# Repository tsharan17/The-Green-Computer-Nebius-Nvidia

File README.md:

<div align="center">

# The Green Computer

## ***"The Sustainable Tech of 21st Century"***

**See how an AI model will run on your hardware, before you build it.**<br>
Predict latency, power, heat, throttling, cost and carbon. Get ranked fixes. Verify. Export.

**[Try it live](https://green-computer-7yy6xwxdna-ue.a.run.app)** ·
**[Two-minute tour](docs/demo-guide.md)** ·
**[Architecture](docs/architecture.md)** ·
**[Run it yourself](#run-it-yourself)**

<table>
  <tr>
    <td align="center" width="25%"><h3>🔮 Predict</h3><sub>Power, heat and throttling solved together, <b>before the hardware exists</b></sub></td>
    <td align="center" width="25%"><h3>💡 Recommend</h3><sub>Ranked fixes across model, software, settings, board and cooling</sub></td>
    <td align="center" width="25%"><h3>⚡ See the impact</h3><sub>Click a change: the engine <b>re-runs everything</b> and shows today vs with the change</sub></td>
    <td align="center" width="25%"><h3>🛡️ Trust it</h3><sub>Nemotron explains; the engine computes. A guardrail rejects any invented number</sub></td>
  </tr>
</table>

> **What is new:** a co-design loop where **NVIDIA Nemotron proposes ideas but a deterministic physics
> engine evaluates every one**, so each recommendation arrives with its own computed before/after.
> [Read why it is innovative ›](#why-it-is-innovative)

*Nebius x NVIDIA Global AI Hackathon, Best Apps and Agents track*

</div>

---

## Contents

[The problem](#the-problem) · [See it](#see-it) · [Try it live](#try-it-live-in-two-minutes) ·
[Nemotron and Token Factory](#built-on-nvidia-nemotron-and-nebius-token-factory) ·
[Why it is different](#why-it-is-different) · [Innovation](#why-it-is-innovative) · [Recommendations](#recommendations-see-the-impact-of-every-change) · [Features](#features) · [How it works](#how-it-works) ·
[Run it yourself](#run-it-yourself) · [Tests](#tests) · [Status](#what-is-and-is-not-verified) ·
[Tech stack](#tech-stack) · [Licence](#licence)

## The problem

> [!IMPORTANT]
> Teams put AI on robots, cameras and edge boards, then discover **too late** that the model
> overheats, throttles itself, blows the power budget or sits on the wrong board. Fixing it means
> weeks of trial and error across the model, the software and the hardware.

**The Green Computer shows it before anything is built.** The bundled example, a YOLOv8s detector on
a Jetson Orin NX at 30 inputs a second in a 40 °C room:

| | Today | With the recommended plan |
|---|:---:|:---:|
| **Verdict** | ❌ Fails | ✅ Passes every requirement |
| **Chip temperature** | 🔥 90 °C, throttles to ~70% speed | ❄️ within your limits |
| **Power** | baseline | **about 59% less** |
| **Energy per input** | baseline | **-72%** |

Then it exports a report and a recipe of scripts. Everything is vendor-neutral and runs fully
offline; NVIDIA GPUs, Nebius cloud jobs and the AI assistant are optional accelerators.

## See it

<table>
  <tr>
    <td width="50%"><br><sub><b>1. Analyse today's setup.</b> A plain verdict, what limits it, and the numbers against your limits.</sub></td>
    <td width="50%"><br><sub><b>2. Try ranked changes.</b> The engine re-runs everything with each one: -72% energy, 59% less power.</sub></td>
  </tr>
  <tr>
    <td colspan="2"><br><sub><b>3. See why.</b> Board heat map: the compute engine reaches 90 °C and slows itself down to cool off.</sub></td>
  </tr>
</table>

<sub>Screenshots are from a local copy running without a Token Factory key, so the Green Agent box
says it is not configured. In the hosted demo it is on.</sub>

## Try it live in two minutes

Open **[green-computer-7yy6xwxdna-ue.a.run.app](https://green-computer-7yy6xwxdna-ue.a.run.app)**
(free, no payment, no email confirmation), then:

1. **Sign up** and open **Example: YOLOv8s on a robot (30 FPS, 55 W, 40 °C)**.
2. **Analyse.** Today's setup fails: the Jetson Orin NX overheats and throttles to about 70% of its speed.
3. **Recommendations.** Click **Start with the top-ranked change**; the engine re-runs everything with it.
4. **Validation.** Build a plan: it meets every requirement with about 59% less power.
5. **Ask the assistant** (sidebar): Nemotron answers by calling the engine, and every figure is checked.
6. **Datasheet import** (Inputs > Hardware, "Your hardware isn't in the list?"): try "Hailo-8L".
7. **Export** the report and the recipe.

## Built on NVIDIA Nemotron and Nebius Token Factory

The deterministic engine computes every number. **NVIDIA Nemotron models, called at run time through
the Nebius Token Factory inference API** (OpenAI-compatible, `TOKEN_FACTORY_API_KEY`), explain and
suggest. Each tier does the job it suits:

| Nemotron model | Job | Why that model | Code |
|---|---|---|---|
| **Nemotron 3 Ultra** | **Green Agent**: plans, calls the engine as tools, explains results | Multi-step reasoning and tool use | `backend/app/agent/` |
| **Nemotron 3 Super** | **AI candidates**: extra change ideas as schema-checked JSON | Mid-weight reasoning at lower cost | `backend/app/agent/recommender.py` |
| **Nemotron 3 Nano** | **Datasheet import**: reads specs from pages found by **Tavily** | Fast, cheap extraction | `backend/app/agent/datasheet.py`, `backend/app/integrations/tavily.py` |

### How the model is kept honest

```mermaid
flowchart LR
    Q([Your question]) --> A[Nemotron agent]
    A -->|asks| E[Engine tools]
    E -->|numbers + provenance| A
    A --> G{Guardrail}
    G -->|every figure is in a tool result| R([Answer])
    G -->|unsupported figure| X([Rejected])
```

| Guard | What it does |
|---|---|
| 🛡️ **Number guardrail** | Rejects any figure in a reply that is not in a tool result |
| 🔒 **Read-only requirements** | The agent cannot change your limits to make a result pass |
| 🧾 **Schema-checked candidates** | Unknown change ids lose their link, unsupported figures are removed, each is labelled *not evaluated* until the engine runs it |
| 👤 **Human confirmation** | Datasheet values arrive with their source page; a person confirms them |
| 🔌 **Live model matching** | Ids are matched against the provider's own list (`GC_MODEL_ULTRA`, `GC_MODEL_SUPER`, `GC_MODEL_NANO` override). All three are live in the [hosted demo](https://green-computer-7yy6xwxdna-ue.a.run.app) |

### Where Token Factory helped

| | Benefit | In practice |
|---|---|---|
| 🚀 | **No GPU needed to use Nemotron** | Built on a machine without an NVIDIA GPU; one OpenAI-compatible endpoint serves Ultra, Super and Nano to any laptop and the cloud demo |
| ⚖️ | **Right-sized models** | Ultra: tool-calling agent, ~1.4 s for a short reply. Super: six candidates in 12 to 21 s. Nano: whole search-and-extract datasheet import in 45 to 60 s (including Tavily) |
| 🔁 | **Swappable** | `TOKEN_FACTORY_BASE_URL` and `GC_MODEL_*` point the same code at any OpenAI-compatible endpoint; `scripts/check_nebius.py` checks chat and a tool-call round trip |

### Services used

| Service | Use | Status |
|---|---|---|
| Nebius Token Factory + NVIDIA Nemotron (Ultra, Super, Nano) | Agent, candidates, datasheet extraction | Live, verified 27 Oct 2026 |
| Tavily | Datasheet search for hardware not in the library | Live, verified 27 Oct 2026 |
| Nebius Serverless Jobs (NVIDIA GPUs) | Real benchmarks for calibration (`bench/`, `GC_ENABLE_NEBIUS=1`) | Built, not run live |
| Nebius Serverless Endpoints | Hosting the app ([deploy/endpoint.md](deploy/endpoint.md)) | Built, not run live |
| Google Cloud Run + Neon PostgreSQL | Hosts the public demo ([deploy/cloudrun/](deploy/cloudrun/README.md)) | Live |

Nebius Serverless Jobs and Endpoints are documented in [docs/connecting-nebius.md](docs/connecting-nebius.md)
and off by default (`GC_ENABLE_NEBIUS=0`).

## Why it is different

<table>
  <tr>
    <td width="25%" valign="top"><h3>📏 Honest numbers</h3>Every metric carries a <code>low..high</code> range and a source: analytical, calibrated, measured, vendor spec or assumed. Predictions are never shown as measurements.</td>
    <td width="25%" valign="top"><h3>🧮 The model never invents</h3>The language model explains and proposes. The engine decides, and every figure is traceable to a tool result.</td>
    <td width="25%" valign="top"><h3>🧭 One coherent path</h3>Inputs, verification, analysis, recommendations, validation, export: a numbered stepper, Back / Next on every page, example projects, light and dark themes.</td>
    <td width="25%" valign="top"><h3>🚧 Clear about gaps</h3>Unsupported inputs (schematic, PCB, RTL, netlist, assembly) get a "planned" message naming the format needed, never a fake success. Requirements are never loosened to pass.</td>
  </tr>
</table>

## Why it is innovative

Most tools answer one question about one layer: a profiler measures a model on hardware you already
own, a simulator models a chip, a spreadsheet adds up watts. The Green Computer closes the loop across
all of them **before the hardware exists**, in a single path.

| | Typical tools | **The Green Computer** |
|---|---|---|
| **When you learn about heat and throttling** | After you buy and run the board | Before: power, temperature and throttling are solved together |
| **Scope** | One layer: the model, or the runtime, or the chip | Model, software, hardware settings, board and cooling choice in one search |
| **What you get** | A number, or a dashboard | A verdict, the limiting factor, ranked fixes, and the re-analysed result of each |
| **Trust** | A single figure | A `low..high` range with provenance on every metric; predicted and measured never mixed |
| **Role of AI** | Often a chatbot that may invent figures | Nemotron explains and proposes; a guardrail rejects any number the engine did not compute |
| **Vendor lock-in** | Tied to one vendor's silicon | Vendor-neutral library of boards, MCUs, FPGAs and accelerators, or describe your own |
| **Outcome** | Insight | A report, a plan and a recipe of scripts you can act on |

What is new, in one line: **a co-design loop where a language model proposes ideas but a deterministic
physics engine evaluates every one of them, so each recommendation arrives with its own computed
before/after, not a guess.** (We make no claim that nothing similar exists anywhere; this is the
combination we built and verified, with its limits stated below.)

## Recommendations: see the impact of every change

Recommendations are the heart of the app. Nothing is suggested without being **evaluated**: click any
change and the engine re-runs the whole analysis with it applied, so you see the consequence on your
system, not a rule of thumb.

```mermaid
flowchart LR
    A[Today's setup<br/>❌ fails] --> B[Ranked changes<br/>5 levels]
    B -->|click one| C[Engine re-runs<br/>the full analysis]
    C --> D[New verdict +<br/>what moved]
    D --> E[Same four figures<br/>today vs with the change]
    E -->|combine changes| F[Plan: each alone<br/>vs together vs today]
    F --> G[Export report<br/>+ recipe scripts]
```

| Level | Example changes | What you see change |
|---|---|---|
| 🧠 **The AI model** | Quantise (FP16 / INT8), prune, smaller input, a lighter model | Energy, throughput, accuracy risk |
| ⚙️ **How it runs** | Batching, runtime options | Latency, throughput, memory |
| 🎛️ **Hardware settings** | Power mode, clocks | Power, temperature, throttling |
| 🔌 **Hardware or cooling** | Another board, a bigger heatsink or other cooling | Steady-state temperature, headroom |
| 💡 **Chip and board ideas** | Directional what-ifs, labelled as such | Direction of change only |

**What the impact view shows, for each change you try:**

- the **new verdict** (fails to passes, or what still fails and why),
- **what moves**: latency, energy per input, power, peak temperature, throttling, cost and carbon,
- the **same four figures side by side, today and with the change**: board heat map, warm-up curve,
  where the energy goes, and power over a batch,
- a **confidence level** and the range on every number.

In the bundled example the top-ranked plan turns a failing Jetson Orin NX into a pass with
**-72% energy and about 59% less power**, and the plan builder shows each change alone and all of
them together against today. Changes are ranked to fix failing requirements first, then your
priority, and each unit of engineering effort costs a little in the ranking so a physical change has
to earn its place. Requirements are never loosened to make a result pass.

## Features

<details open>
<summary><b>The six-step path</b></summary>

1. **Workspace.** Create an account; projects live in a private or a team workspace. Every change of
   inputs is a version; every analysis, plan, upload and export is in the project's history.
2. **Model and hardware.** Upload an ONNX model (validated, with a graph summary) or pick one of the
   library models; pick a board, MCU, FPGA or accelerator from the library or describe your own.
   Each hardware category lists exactly which files it accepts: device profiles (YAML/JSON, values
   may carry units), Vivado / ST Edge AI / Vela reports, power and telemetry logs, firmware ELF
   files, datasheets (read offline; scans go to OCR when installed, otherwise manual review).
3. **Constraints and environment.** Throughput, power, latency, memory and accuracy limits; ambient
   temperature, cooling, hours of use, electricity price and grid carbon; how it runs today.
4. **Analysis (of today's setup only).** The verdict, what limits it, the numbers against your
   limits, and four figures: a board heat map, the warm-up curve, where the energy goes and power
   over one batch. Optional detail views: **system map**, **execution timeline**, **memory map**,
   **thermal and cooling** and **energy and performance**.
5. **Recommendations: try changes.** Changes at five levels: the AI model, how it runs, hardware
   settings, hardware or cooling choice, and directional chip/board ideas, ranked for your
   requirements. Click one and the engine re-runs the analysis with it. Optionally ask Nemotron for
   more candidates; nothing it proposes is applied until the engine evaluates it.
6. **Validation and export.** Combine changes into a plan; the engine re-analyses today, each change
   alone and the combination. Run the model on the server's CPU (ONNX Runtime, isolated and
   time-limited) for measured latency; import measurements (bench JSON, CSV, nvidia-smi, tegrastats);
   compare predicted with measured. Export the report (Markdown, HTML, PDF), plan JSON, comparisons,
   traces, a hardware change specification, deployment configuration, recipe scripts, and an INT8
   ONNX model when quantisation runs and its outputs match the original.

</details>

<details>
<summary><b>Honesty rules</b></summary>

- Every number carries its range and its source. Predicted traces are labelled predicted; only real
  runs or imported logs are measured, and the two are never mixed.
- Exports are labelled *generated and validated*, *generated* or *template*. No changed PCB, RTL or
  chip-design file is ever produced; chip and board ideas are directional what-ifs.
- Accuracy effects of quantisation or pruning are priors with stated risk, never promises.
- The optional AI assistant cannot produce numbers; the engine computes all of them.

</details>

## How it works

```mermaid
flowchart LR
    U([Browser<br/>React + Vite]) -->|/api/v1| API[FastAPI<br/>auth, tenancy, services]
    API --> ENG[Engine<br/>roofline, power-temperature-<br/>throttling solver, search]
    API --> TWIN[Digital twin<br/>predicted and measured traces]
    API --> DB[(SQLite or<br/>PostgreSQL)]
    API --> EXEC[Isolated worker<br/>ONNX Runtime benchmark,<br/>INT8 quantisation]
    API -->|tool calls, JSON| TF[Nebius Token Factory<br/>NVIDIA Nemotron<br/>Ultra / Super / Nano]
    TF -.->|explains, proposes| API
    API -->|datasheet search| TV[Tavily]
    EXEC -.->|optional| NB[Nebius Serverless Jobs<br/>NVIDIA GPUs]
```

The engine is pure and deterministic (no network, no LLM). The Nemotron layer sits beside it and can
only call it as a tool. The full description, with a status for each part, is in
[docs/architecture.md](docs/architecture.md).

<details>
<summary><b>Repository map</b></summary>

| Path | What is in it |
|---|---|
| `backend/app/engine/` | Physics, search and advice (pure, deterministic) |
| `backend/app/twin/` | Digital twin: execution trace, tensor lifetimes, memory timeline |
| `backend/app/agent/` | Nemotron on Token Factory: agent, recommender, datasheet import, guardrail |
| `backend/app/api/v1/`, `services/`, `db/`, `auth/` | API, orchestration, models, accounts and tenancy |
| `backend/app/execution/` | Isolated worker: benchmark, quantise, compare |
| `backend/app/migrations/` | Alembic revisions |
| `frontend/src/` | React app and hand-built SVG charts (`twin/chart.tsx`) |
| `frontend/e2e/` | Playwright browser journeys and accessibility checks |
| `bench/` | Benchmark scripts for GPU hosts (Nebius Serverless Jobs) |
| `deploy/`, `Dockerfile`, `docker-compose.yml` | Cloud Run, Nebius endpoint and compose deployment |
| `scripts/` | Dev start, acceptance, demo data, API docs |
| `docs/` | Architecture, API, security, assumptions, demo guide |

</details>

## Run it yourself

The hosted demo needs none of this. To run your own copy you need Python 3.11+ and Node.js 20+.

**Fastest:**
- **Windows:** double-click **`Start The Green Computer.bat`**.
- **macOS / Linux:** `./start.sh`

It creates the environment, builds the interface and opens http://localhost:8000. The first start
takes a few minutes; later starts take seconds. Options: `--port 8080`, `--rebuild`, `--no-browser`.

**Developer setup:**

```powershell
scripts/dev.ps1          # Windows: installs, builds the UI, serves http://localhost:8000
```
```bash
scripts/dev.sh           # macOS / Linux / Git Bash
```

Create an account (it comes with an example project) and press **Analyse**. Optional:
`python scripts/demo_data.py http://localhost:8000` fills a demo account with analysed projects, a
plan, exports and a local run.

**Switch on Nemotron.** Copy `.env.example` to `.env`, set `TOKEN_FACTORY_API_KEY` (and
`TAVILY_API_KEY` for datasheet search), restart, then run `python scripts/check_nebius.py`. Without a
key everything else still works. Never commit `.env`.

**Docker / PostgreSQL:** `docker compose up --build` (see `docker-compose.yml`). The public demo runs
this repository's image on Google Cloud Run with Neon PostgreSQL; see
[deploy/cloudrun/README.md](deploy/cloudrun/README.md). Configuration is by environment variables;
`.env.example` lists every one.

## Tests

```bash
cd backend && .venv/Scripts/python -m pytest -q        # 346 unit, API and integration tests (PostgreSQL with GC_TEST_PG_URL)
cd backend && .venv/Scripts/python -m ruff check . && .venv/Scripts/python -m mypy app
cd frontend && npm run lint && npm run build && npx playwright test   # 15 browser journeys + axe accessibility
python scripts/acceptance.py http://localhost:8000     # end-to-end check against a running server
```

(On macOS / Linux use `.venv/bin/python`.) More: [IMPLEMENTATION_STATUS.md](IMPLEMENTATION_STATUS.md),
[docs/api.md](docs/api.md), [docs/security.md](docs/security.md), [docs/assumptions.md](docs/assumptions.md).

## What is and is not verified

<details open>
<summary><b>Status of each part</b></summary>

| Piece | Status |
|---|---|
| Engine, API, accounts, tenancy, intake, twin, plans, exports | Tested: backend unit/API/integration tests, Playwright browser journeys, axe accessibility checks, acceptance script |
| PostgreSQL | Migrations and a full journey tested against PostgreSQL 16; SQLite is the local default |
| Local execution | Real ONNX Runtime CPU runs tested; measures latency and operator time, not power or temperature |
| Predictions | Analytical with stated assumptions; the only measurements so far are CPU latencies on the development machine. **No Jetson, GPU or power measurement exists yet**, so Jetson results are predictions with ranges |
| CUDA / TensorRT backends | Detected and gated; never run here (no NVIDIA GPU) |
| Green Agent (Token Factory) | Tested with mocked providers. **Live** on 27 Oct 2026 with `nvidia/Nemotron-3-Ultra-550b-a55b`: the agent answered, and `scripts/check_nebius.py` passed chat and a tool-call round trip. Off unless a key is set |
| AI recommendation candidates | Tested with mocked providers. **Live** on 27 Oct 2026 with `nvidia/nemotron-3-super-120b-a12b`: the first two attempts failed (invalid JSON, then no answer because a reasoning model used up its token budget). After the fix (JSON repair, one retry, more room), 4 of 4 runs succeeded |
| Datasheet web search (Tavily + Nemotron) | Tested with fakes. **Live** on 27 Oct 2026 with `nvidia/NVIDIA-Nemotron-3-Nano-30B-A3B`: the first runs failed the same two ways and got the same fix. After that, four real devices were drafted with each value sourced, and one was confirmed and analysed |
| Nebius Serverless Jobs and Endpoints | Scripts built from vendor documentation; **never run live** |
| Terms, privacy and acceptable-use pages | Written to match the implementation; **draft, needs professional legal review** |
| OCR for scanned PDFs | Implemented; untested here (no Tesseract installed) |
| Docker image / Cloud Run + Neon | Built by Cloud Build and running as the public demo (deployed 27 Oct 2026). The compose stack is written but not run |
| Recipes and deployment configs | Templates; syntax-checked, not run on devices |
| Chip/board what-ifs | Directional analytical what-ifs, not designs |

</details>

## Tech stack

Python 3.11 · FastAPI · SQLAlchemy + Alembic · NumPy · ONNX / ONNX Runtime · React · TypeScript · Vite ·
Playwright · Docker · Google Cloud Run · Neon PostgreSQL · **NVIDIA Nemotron on Nebius Token Factory** ·
**Tavily**

## Licence

[Apache-2.0](LICENSE).

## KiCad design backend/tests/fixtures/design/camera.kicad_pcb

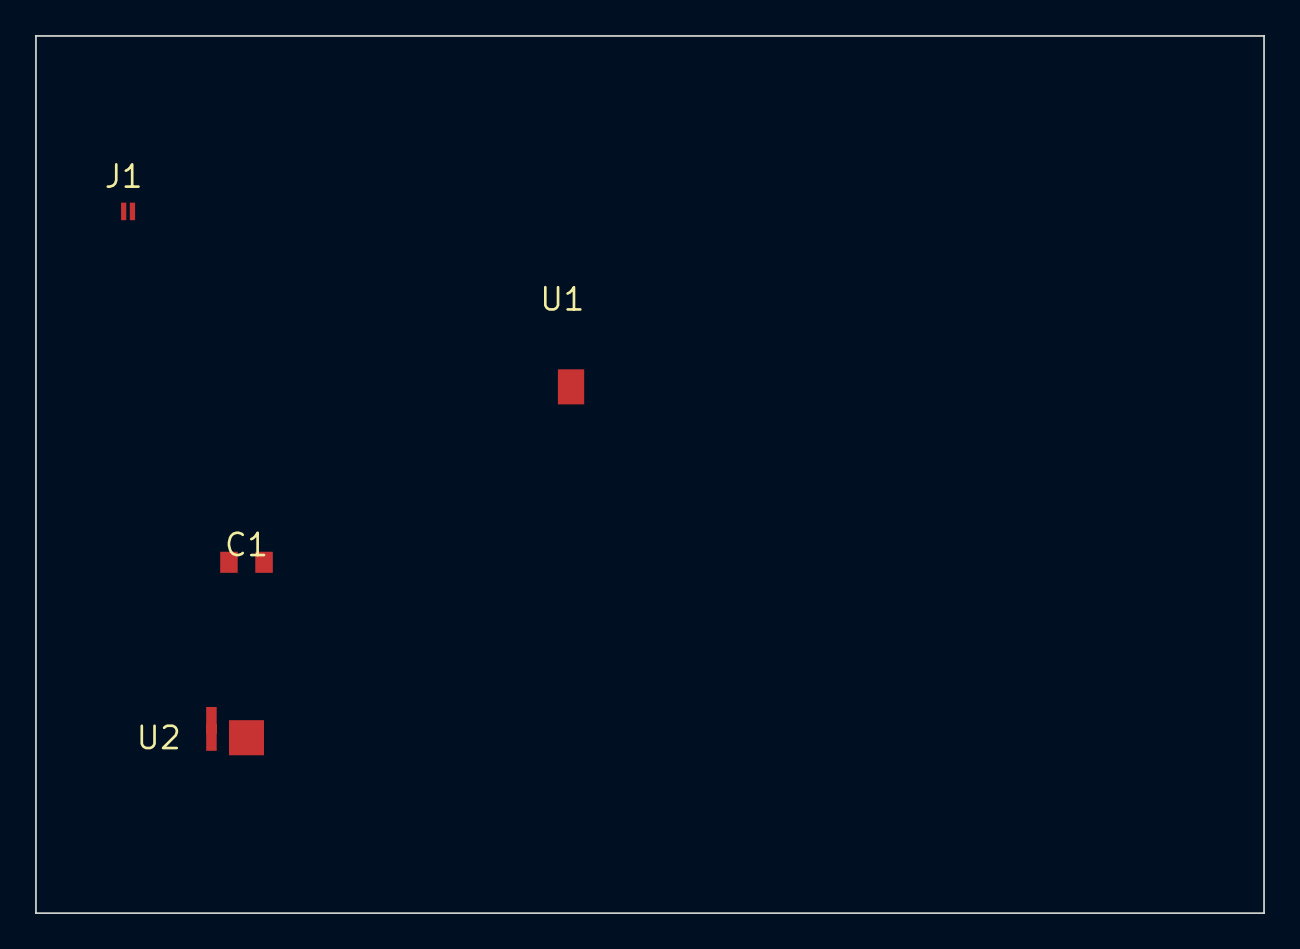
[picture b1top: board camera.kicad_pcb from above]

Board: 4 copper layers, 70.0 x 50.0 mm, 5 parts (1 on the bottom side), 4 nets, no tracks yet.

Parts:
C1: 22u; C_0805
J1: CSI camera; FFC_15P
R1: 10k; R_0402
U1: Jetson Orin Nano 8GB; SODIMM-260
U2: TPS54560; HTSOP-8

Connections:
FB: R1.1, U2.2
GND: C1.2, J1.2, R1.2, U1.1, U2.9
MIPI_CLK_P: J1.1, U1.3
VDD_5V: C1.1, U1.2, U2.1

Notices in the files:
README.md:
License: Apache-2.0
